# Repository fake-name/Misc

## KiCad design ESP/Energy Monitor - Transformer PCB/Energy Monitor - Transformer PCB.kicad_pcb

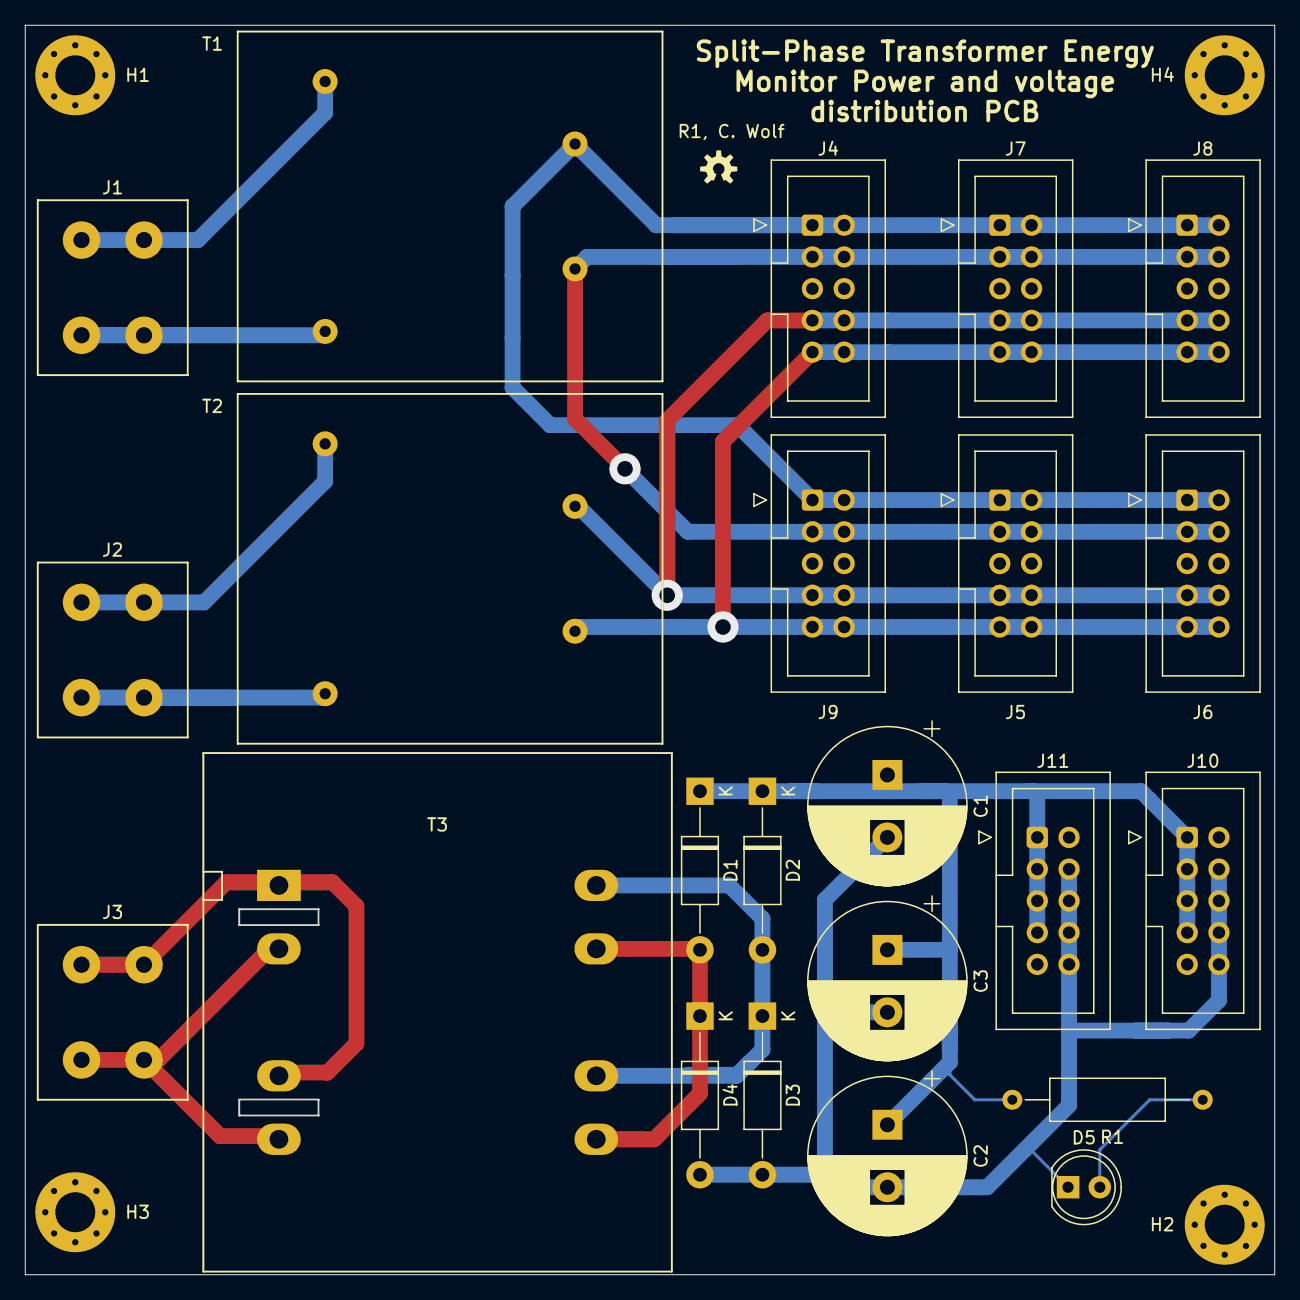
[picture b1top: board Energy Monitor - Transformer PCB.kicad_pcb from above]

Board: 2 copper layers, 100.0 x 100.0 mm, 27 parts (0 on the bottom side), 15 nets.

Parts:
C1, C2, C3: CP1; CP_Radial_D12.5mm_P5.00mm
D1, D2, D3, D4: D; D_DO-41_SOD81_P12.70mm_Horizontal
D5: LED; LED_D5.0mm_Clear
H1, H2, H3, H4: MountingHole; MountingHole_3.2mm_M3_Pad_Via
J1, J2, J3: Conn_01x02; WE 691411410002 - 2 Pin Wire-To-Board Terminal Block
J4, J5, J6, J7, J8, J9, J10, J11: Conn_02x05_Odd_Even; IDC-Header_2x05_P2.54mm_Vertical
R1: 1K; R_Axial_DIN0309_L9.0mm_D3.2mm_P15.24mm_Horizontal
T1, T2: EI30-15.5; EI30-15.5-TH
T3: AHI050; AHI050-TH

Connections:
+9V: C1.1, C2.1, C3.1, D1.1, D2.1, J10.1, J10.3, J10.5, J10.7, J11.1, J11.3, J11.5, J11.7, R1.1
GND: C1.2, C2.2, C3.2, D3.2, D4.2, D5.1, J10.4, J10.6, J10.8, J10.10, J11.4, J11.6, J11.8, J11.10
unnamed: D1.2, D4.1, T3.6, T3.8
unnamed: D2.2, D3.1, T3.5, T3.7
unnamed: D5.2, R1.2
unnamed: J1.1, T1.1
unnamed: J1.2, T1.5
unnamed: J2.1, T2.1
unnamed: J2.2, T2.5
unnamed: J3.1, T3.1, T3.3
unnamed: J3.2, T3.2, T3.4
unnamed: J4.1, J4.2, J5.1, J5.2, J6.1, J6.2, J7.1, J7.2, J8.1, J8.2, J9.1, J9.2, T1.9
unnamed: J4.3, J4.4, J5.3, J5.4, J6.3, J6.4, J7.3, J7.4, J8.3, J8.4, J9.3, J9.4, T1.7
unnamed: J4.7, J4.8, J5.7, J5.8, J6.7, J6.8, J7.7, J7.8, J8.7, J8.8, J9.7, J9.8, T2.9
unnamed: J4.9, J4.10, J5.9, J5.10, J6.9, J6.10, J7.9, J7.10, J8.9, J8.10, J9.9, J9.10, T2.7

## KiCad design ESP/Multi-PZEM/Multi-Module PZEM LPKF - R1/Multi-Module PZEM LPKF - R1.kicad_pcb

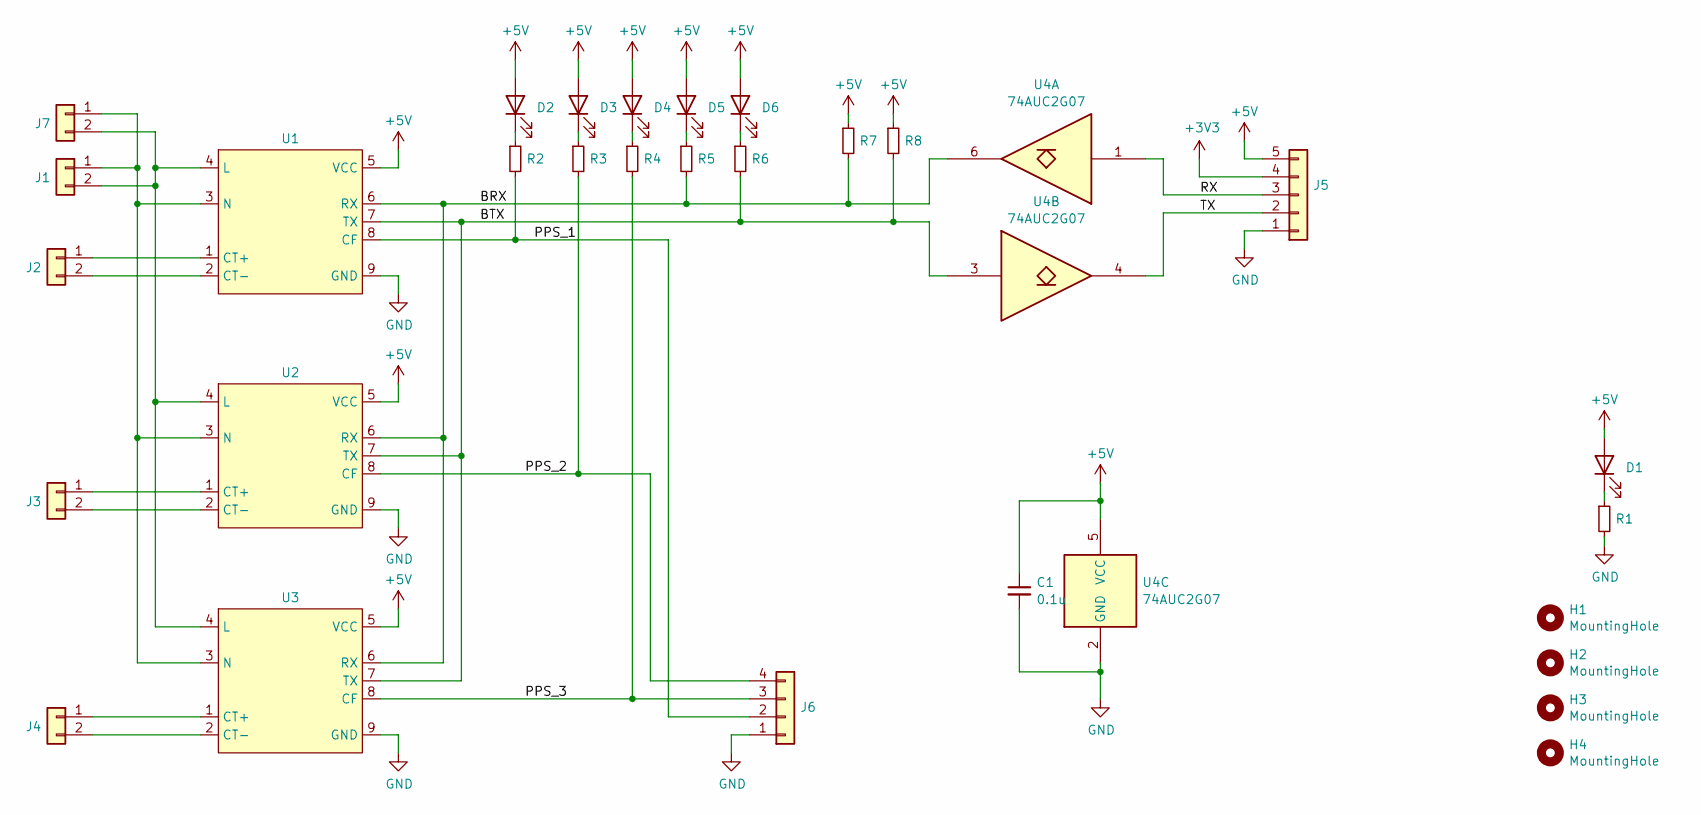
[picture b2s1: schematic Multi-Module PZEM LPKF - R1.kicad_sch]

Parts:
C1: 0.1u; C_0603_1608Metric
D1, D2, D3, D4, D5, D6: LED; LED_0603_1608Metric
H1, H2, H3, H4: MountingHole; MountingHole_3.2mm_M3_Pad_Via
J1: Conn_01x02; WE 691411410002 - 2 Pin Wire-To-Board Terminal Block
J2, J3, J4: Conn_01x04; JST_XH_B2B-XH-A_1x02_P2.50mm_Vertical
J5: Conn_01x05; JST_XH_B5B-XH-A_1x05_P2.50mm_Vertical
J6: Conn_01x05; JST_XH_B4B-XH-A_1x04_P2.50mm_Vertical
J7: Conn_01x02; PhoenixContact_MC_1,5_2-G-5.08_1x02_P5.08mm_Horizontal
R1, R2, R3, R4, R5, R6, R7, R8: R_Small; R_0603_1608Metric
U1, U2, U3: PZEM-004T-100A-D-P
U4: 74AUC2G07; SOT-23-6_Handsoldering

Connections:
+3V3: J5.4
+5V: C1.1, D1.2 (A), D2.2 (A), D3.2 (A), D4.2 (A), D5.2 (A), D6.2 (A), J5.5, R7.1, R8.1, U1.5 (VCC), U2.5 (VCC), U3.5 (VCC), U4.5 (VCC)
/BRX: R5.2, R7.2, U1.6 (RX), U2.6 (RX), U3.6 (RX), U4.6
/BTX: R6.2, R8.2, U1.7 (TX), U2.7 (TX), U3.7 (TX), U4.3
/PPS_1: J6.2, R2.2, U1.8 (CF)
/PPS_2: J6.4, R3.2, U2.8 (CF)
/PPS_3: J6.3, R4.2, U3.8 (CF)
/RX: J5.3, U4.1
/TX: J5.2, U4.4
GND: C1.2, J5.1, J6.1, R1.2, U1.9 (GND), U2.9 (GND), U3.9 (GND), U4.2 (GND)
unnamed: D1.1 (K), R1.1
unnamed: D2.1 (K), R2.1
unnamed: D3.1 (K), R3.1
unnamed: D4.1 (K), R4.1
unnamed: D5.1 (K), R5.1
unnamed: D6.1 (K), R6.1
unnamed: J1.1, J7.1, U1.3 (N), U2.3 (N), U3.3 (N)
unnamed: J1.2, J7.2, U1.4 (L), U2.4 (L), U3.4 (L)
unnamed: J2.1, U1.1 (CT+)
unnamed: J2.2, U1.2 (CT-)
unnamed: J3.1, U2.1 (CT+)
unnamed: J3.2, U2.2 (CT-)
unnamed: J4.1, U3.1 (CT+)
unnamed: J4.2, U3.2 (CT-)

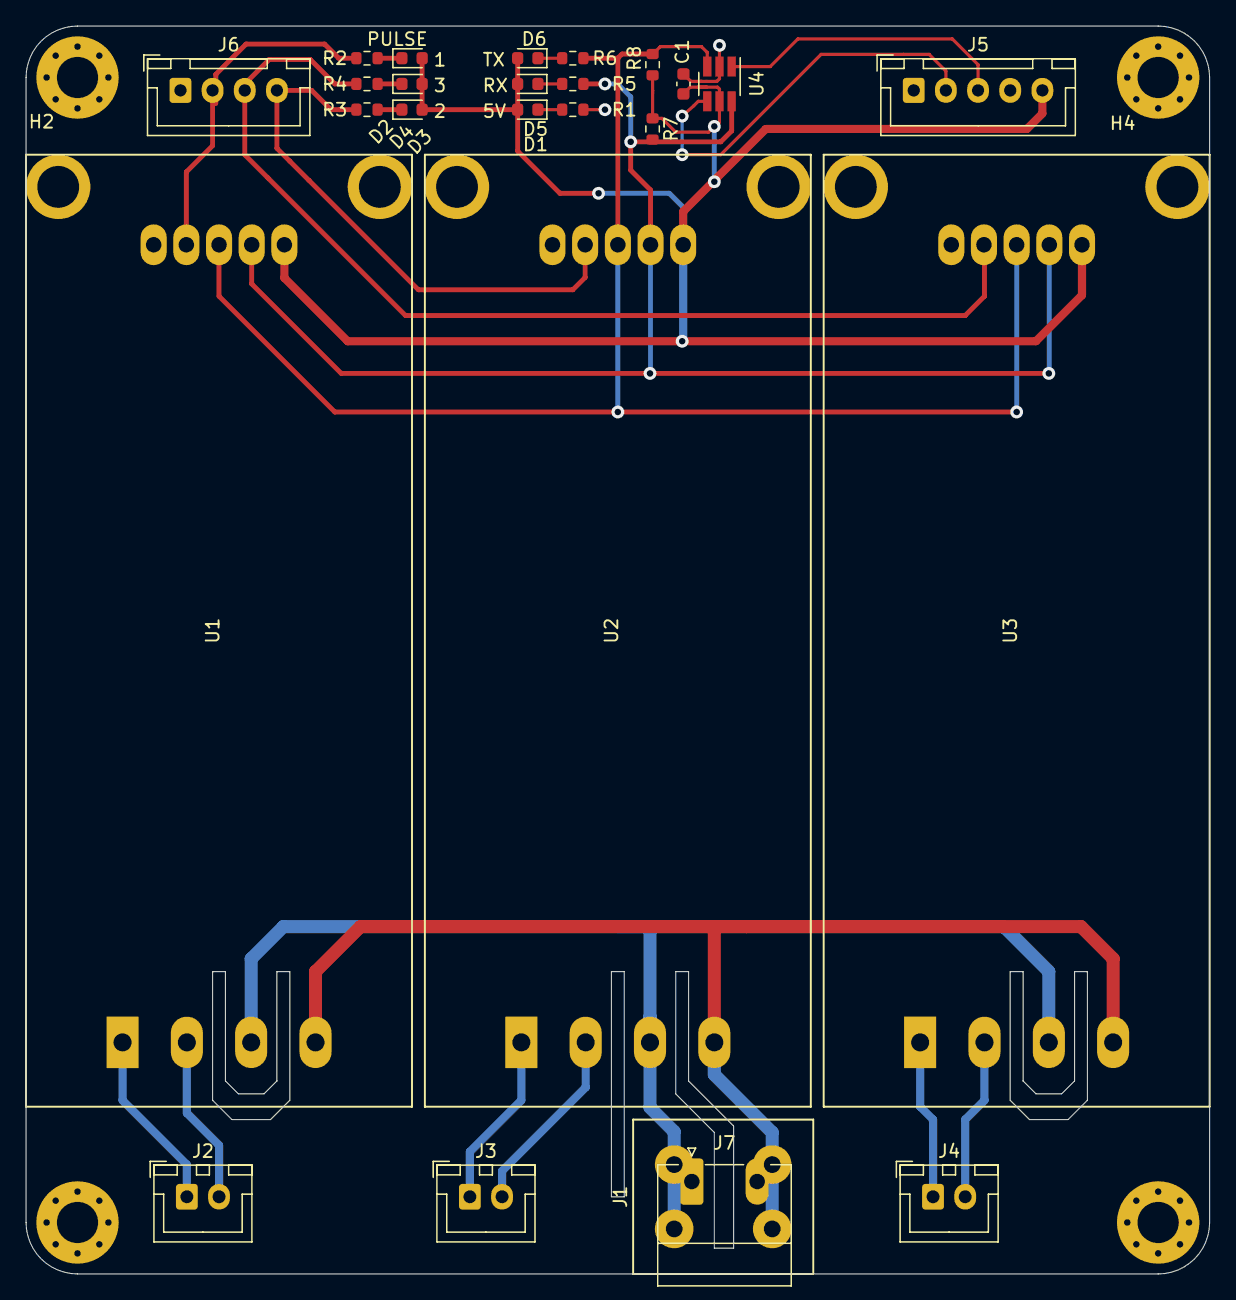
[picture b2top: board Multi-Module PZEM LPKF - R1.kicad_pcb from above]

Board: 2 copper layers, 92.0 x 97.0 mm, 30 parts (0 on the bottom side), 23 nets.

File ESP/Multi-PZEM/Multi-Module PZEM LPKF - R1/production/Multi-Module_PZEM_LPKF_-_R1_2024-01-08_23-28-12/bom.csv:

Designator,Footprint,Quantity,Value,LCSC Part #
C1,0603,1,0.1u,
"D1, D2, D3, D4, D5, D6",0603,6,LED,
"H1, H2, H3, H4",MountingHole_3.2mm_M3_Pad_Via,4,MountingHole,
J1,WE 691411410002 - 2 Pin Wire-To-Board Terminal Block,1,Conn_01x02,
"J2, J3, J4",JST_XH_B2B-XH-A_1x02_P2.50mm_Vertical,3,Conn_01x04,
J5,JST_XH_B5B-XH-A_1x05_P2.50mm_Vertical,1,Conn_01x05,
J6,JST_XH_B4B-XH-A_1x04_P2.50mm_Vertical,1,Conn_01x05,
J7,"PhoenixContact_MC_1,5_2-G-5.08_1x02_P5.08mm_Horizontal",1,Conn_01x02,
"R1, R2, R3, R4, R5, R6, R7, R8",0603,8,R_Small,
"U1, U2, U3",PZEM-004T-100A-D-P,3,~,
U4,SOT-23-6_Handsoldering,1,74AUC2G07,

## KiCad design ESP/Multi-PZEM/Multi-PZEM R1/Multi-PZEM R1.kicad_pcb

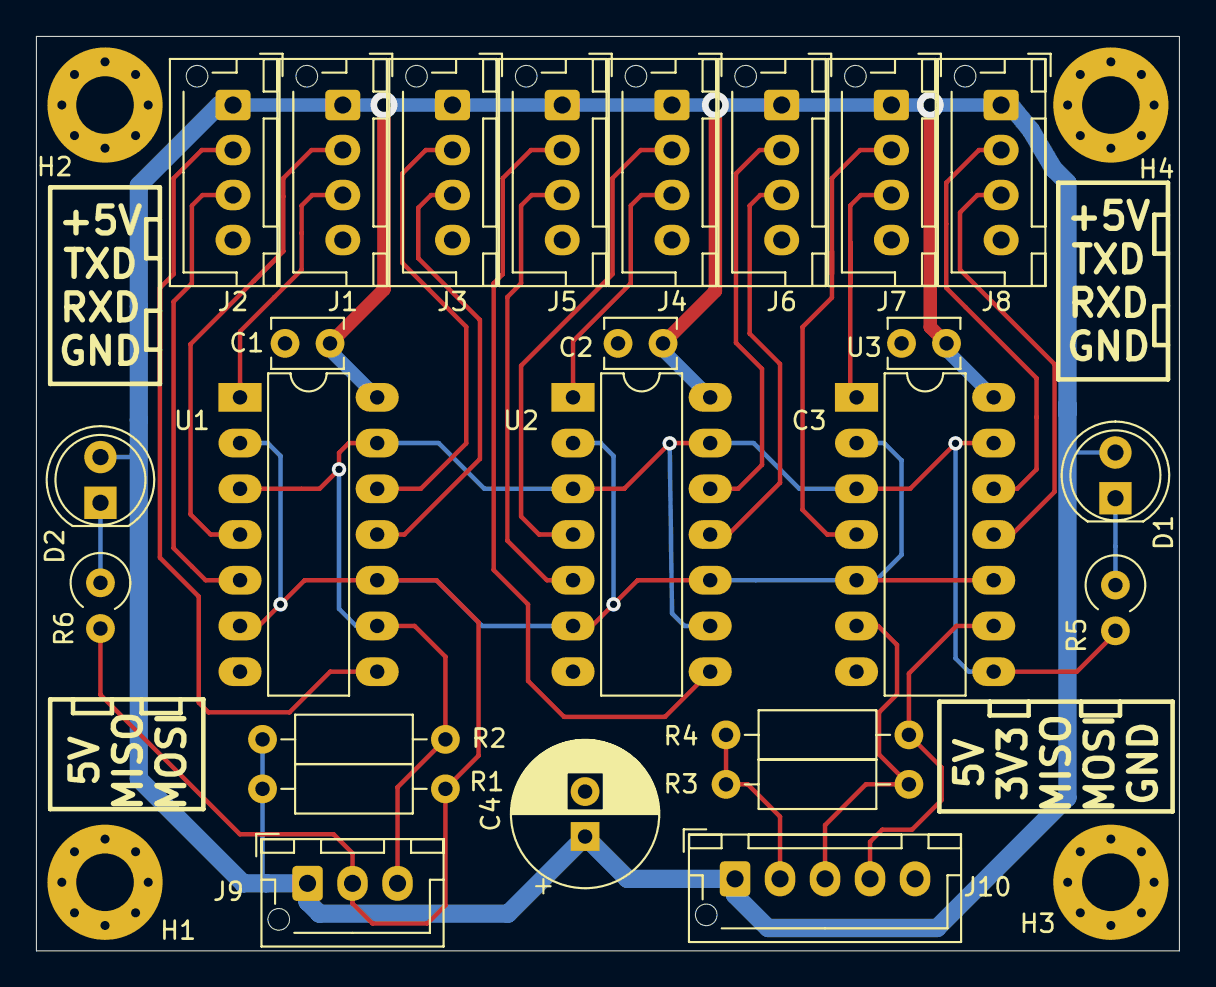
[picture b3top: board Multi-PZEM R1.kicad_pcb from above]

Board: 2 copper layers, 63.5 x 50.8 mm, 29 parts (0 on the bottom side), 25 nets.

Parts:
C1, C2, C3: CP1_Small; C_Disc_D3.8mm_W2.6mm_P2.50mm
C4: CP; CP_Radial_D8.0mm_P2.50mm
D1, D2: LED; LED_D5.0mm_Clear
H1, H2, H3, H4: MountingHole; MountingHole_3.2mm_M3_Pad_Via
J1, J2, J3, J4, J5, J6, J7, J8: Conn_01x04; JST_XH_B4B-XH-AM_1x04_P2.50mm_Vertical
J9: Conn_01x04; JST_XH_B3B-XH-AM_1x03_P2.50mm_Vertical
J10: Conn_01x04; JST_XH_B5B-XH-AM_1x05_P2.50mm_Vertical
R1, R2, R3, R4: R_Small; R_Axial_DIN0207_L6.3mm_D2.5mm_P10.16mm_Horizontal
R5, R6: R_Small; R_Axial_DIN0309_L9.0mm_D3.2mm_P2.54mm_Vertical
U1, U2, U3: 74LS07; DIP-14_W7.62mm_LongPads

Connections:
+3V3: J10.2, R3.1, R4.1
+5V: C1.1, C2.1, C3.1, C4.1, D1.2, D2.2, J1.1, J2.1, J3.1, J4.1, J5.1, J6.1, J7.1, J8.1, J9.1, J10.1, R1.1, R2.1, U1.14, U2.14, U3.14
/MISO: J10.3, R3.2, U3.6
/MOSI: J10.4, R4.2, U3.9
/RX-MISO: J9.2, R1.2, R6.2, U1.2, U1.6, U1.10, U2.2, U2.6, U2.10, U3.2, U3.5, U3.10
/TX-MOSI: J9.3, R2.2, R5.2, U1.3, U1.9, U1.13, U2.3, U2.9, U2.13, U3.3, U3.8, U3.13
GND: C1.2, C2.2, C3.2, C4.2, J1.4, J2.4, J3.4, J4.4, J5.4, J6.4, J7.4, J8.4, J10.5, U1.7, U2.7, U3.7
unnamed: D1.1, R5.1
unnamed: D2.1, R6.1
unnamed: J1.2, U1.4
unnamed: J1.3, U1.1
unnamed: J2.2, U1.8
unnamed: J2.3, U1.5
unnamed: J3.2, U1.12
unnamed: J3.3, U1.11
unnamed: J4.2, U2.4
unnamed: J4.3, U2.1
unnamed: J5.2, U2.8
unnamed: J5.3, U2.5
unnamed: J6.2, U2.12
unnamed: J6.3, U2.11
unnamed: J7.2, U3.4
unnamed: J7.3, U3.1
unnamed: J8.2, U3.12
unnamed: J8.3, U3.11

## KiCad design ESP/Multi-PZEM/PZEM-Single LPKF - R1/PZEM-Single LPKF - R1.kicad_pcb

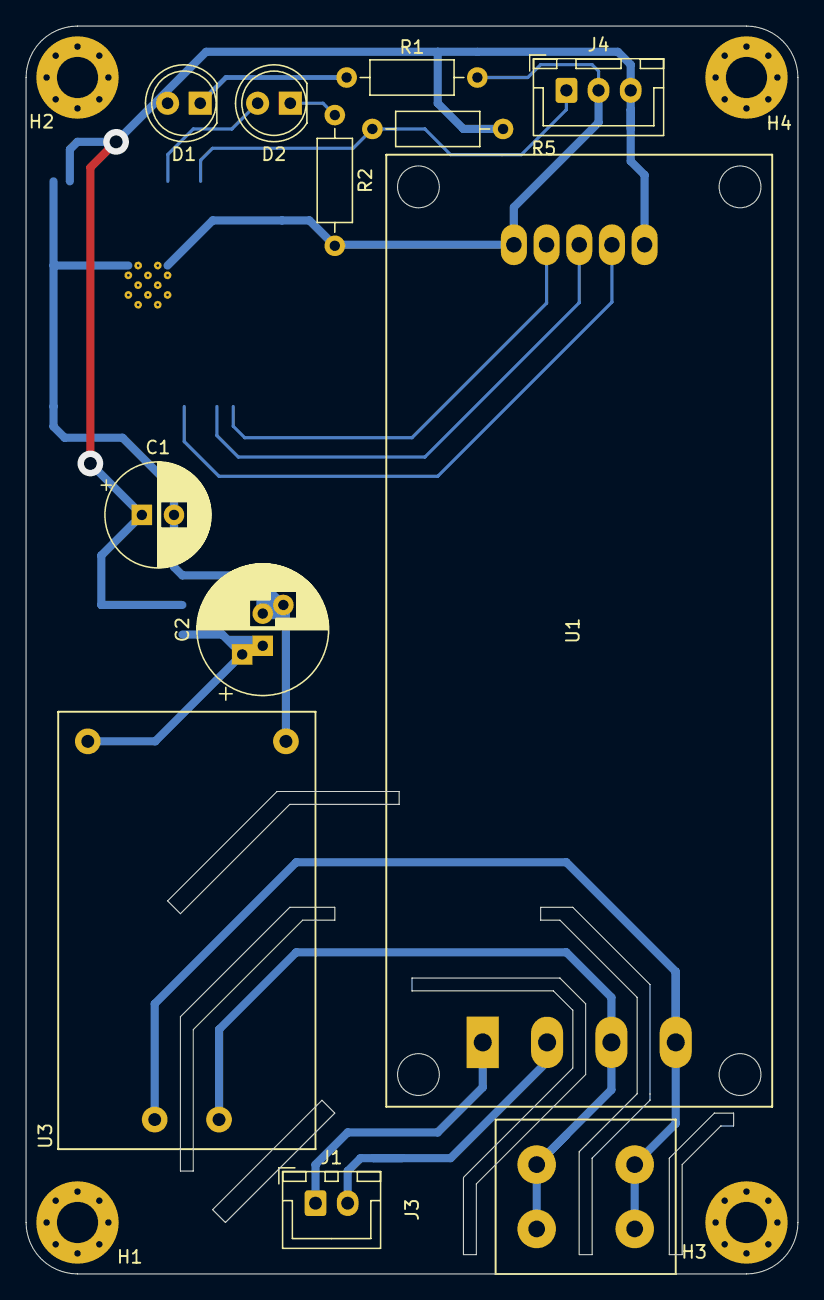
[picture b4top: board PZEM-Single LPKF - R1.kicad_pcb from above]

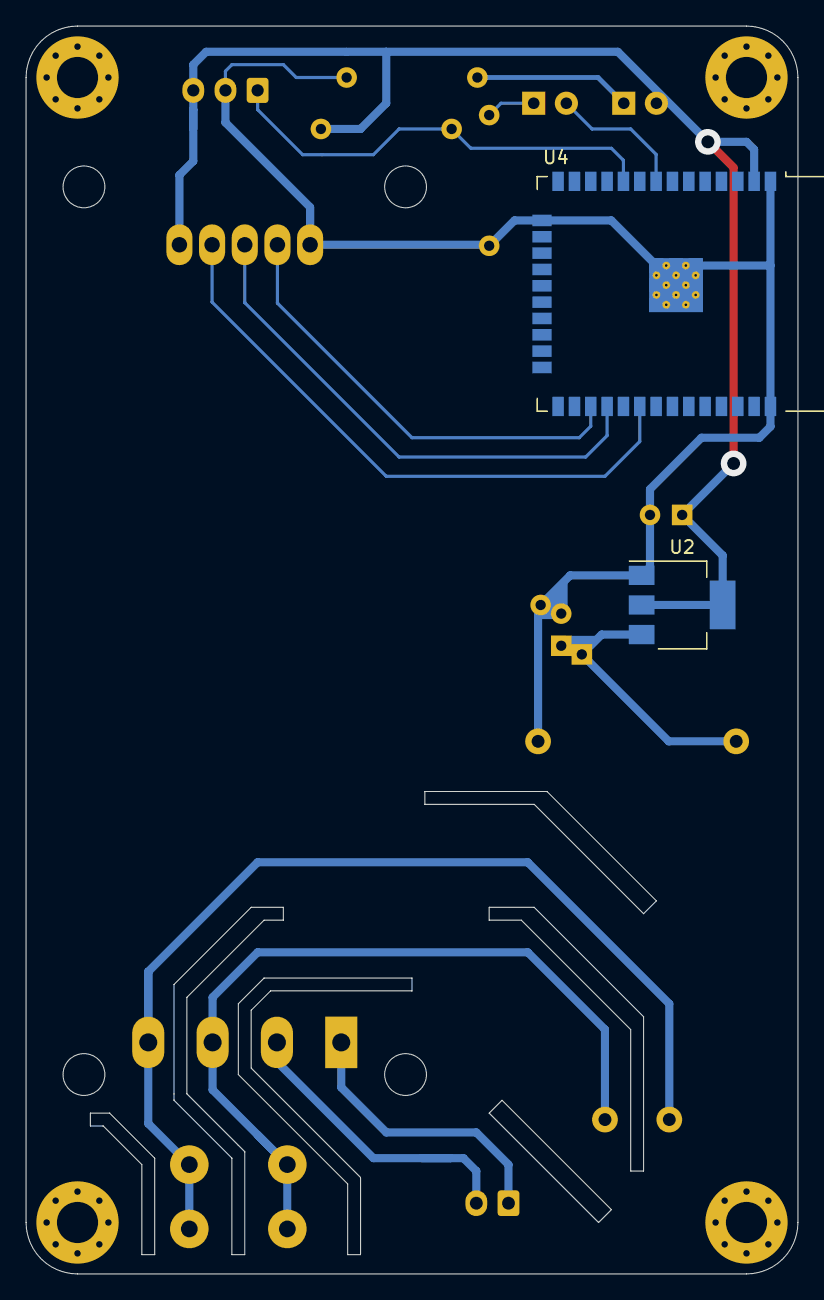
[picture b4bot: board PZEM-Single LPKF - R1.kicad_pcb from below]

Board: 2 copper layers, 60.0 x 97.0 mm, 18 parts (2 on the bottom side), 14 nets.

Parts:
C1: CP; CP_Radial_D8.0mm_P2.50mm
C2: CP; CP_Radial_D10.0mm_P2.50mm_P5.00mm
D1, D2: LED; LED_D5.0mm
H1, H2, H3, H4: MountingHole; MountingHole_3.2mm_M3_Pad_Via
J1: Conn_01x04; JST_XH_B2B-XH-A_1x02_P2.50mm_Vertical
J3: Conn_01x02; WE 691411410002 - 2 Pin Wire-To-Board Terminal Block
J4: Conn_01x04; JST_XH_B3B-XH-A_1x03_P2.50mm_Vertical
R1, R2, R5: R_Small; R_Axial_DIN0207_L6.3mm_D2.5mm_P10.16mm_Horizontal
U1: PZEM-004T-100A-D-P
U2: AMS1117-3.3; SOT-223-3_TabPin2
U3: HLK-PM01
U4: ESP32-WROOM-32

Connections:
+3V3: C1.1, D1.2 (A), J4.3, R5.1, U1.5 (VCC), U2.2 (VO), U4.2 (VDD)
+5V: C2.1, U2.3 (VI), U3.4 (+Vo)
GND: C1.2, C2.2, J4.2, R1.2, R2.2, U1.9 (GND), U2.1 (GND), U3.3 (-Vo), U4.1 (GND), U4.15 (GND), U4.38 (GND), U4.39 (GND)
unnamed: D1.1 (K), R1.1
unnamed: D2.2 (A), U4.8 (IO32)
unnamed: D2.1 (K), R2.1
unnamed: J1.1, U1.1 (CT+)
unnamed: J1.2, U1.2 (CT-)
unnamed: J3.1, U1.4 (L), U3.1 (AC)
unnamed: J3.2, U1.3 (N), U3.2 (AC)
unnamed: J4.1, R5.2, U4.10 (IO25)
unnamed: U1.8 (CF), U4.27 (IO16)
unnamed: U1.6 (RX), U4.30 (IO18)
unnamed: U1.7 (TX), U4.28 (IO17)
